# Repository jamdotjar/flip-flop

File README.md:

# T flip-flop
A transistor based T flip flop circuit. It uses 15 transistors, making 6 NAND gates. The design is based on an edge-triggered D flip-flop with one output fed into Data, and the user input acting as clock.

The design is a direct transfer of the logic-gate design into transistors. Each gate is fully built, which makes this a bit innefficent on part usage, but it's very simple design-wise. ( there's also lights for output, and a button for input ). The main challenge was figuring how to best use the limited resistor selection I had access to, without breaking the circit with a ton of random variance. 

For the PCB, I just tried to fit the schematic inside the logic diagram, to some degree of sucess. The design on the back is the result of asking as many people as possible what they thought should go there. I have ( almost ) no complaints.

I've yet to assemble, but I will update this page once I do.

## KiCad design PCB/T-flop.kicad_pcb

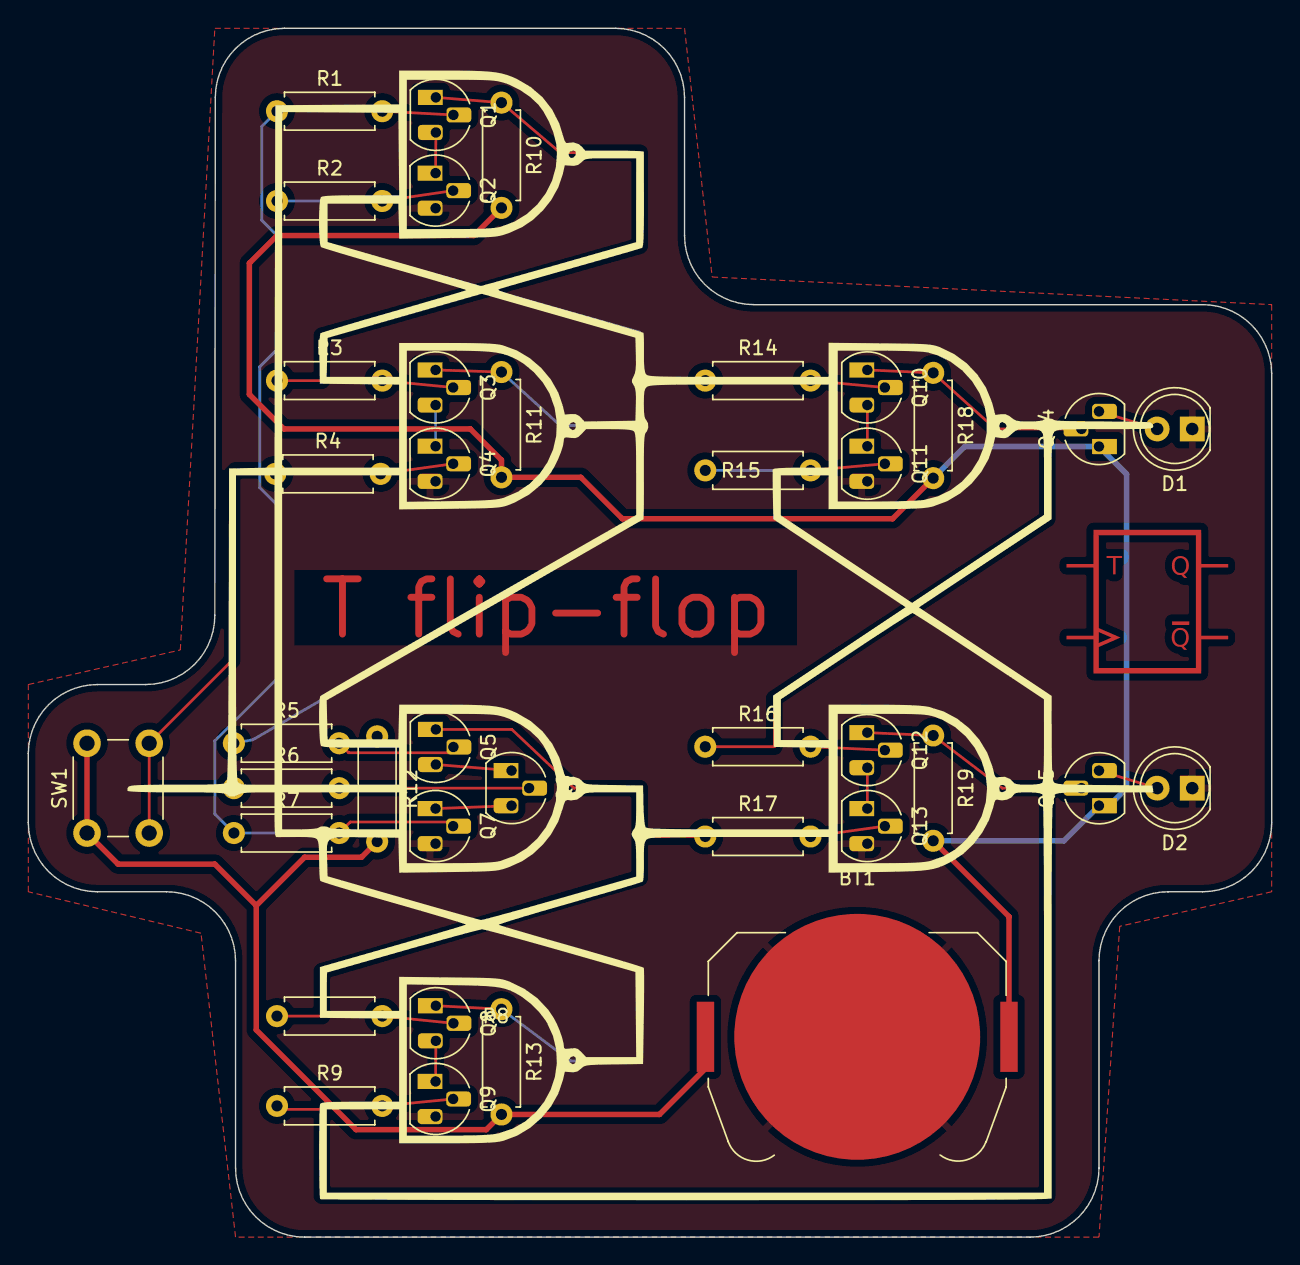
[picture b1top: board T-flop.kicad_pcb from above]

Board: 2 copper layers, 90.0 x 87.5 mm, 39 parts (1 on the bottom side), 31 nets.

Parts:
BT1: Battery_Cell; BatteryHolder_Keystone_3034_1x20mm
D1, D2: LED; LED_D5.0mm
Q1, Q2, Q3, Q4, Q5, Q6, Q7, Q8, Q9, Q10, Q11, Q12, Q13, Q14, Q15: NPN; TO-92L_HandSolder
R1, R2, R14, R15, R16, R17: 4.7k; R_Axial_DIN0207_L6.3mm_D2.5mm_P7.62mm_Horizontal
R3, R4, R5, R6, R7, R8, R10, R11, R12, R13, R18, R19: 220; R_Axial_DIN0207_L6.3mm_D2.5mm_P7.62mm_Horizontal
R9: 47k; R_Axial_DIN0207_L6.3mm_D2.5mm_P7.62mm_Horizontal
SW1: SW_Push; SW_PUSH_6mm
g: LOGO

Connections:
+3.3V: BT1.1 (+), Q14.1 (C), Q15.1 (C), R10.2, R11.2, R12.2, R13.2, R18.2, R19.2, SW1.1
GND: BT1.2 (-), D1.1 (K), D2.1 (K), Q2.3 (E), Q4.3 (E), Q7.3 (E), Q9.3 (E), Q11.3 (E), Q13.3 (E)
unnamed: D1.2 (A), Q14.3 (E)
unnamed: D2.2 (A), Q15.3 (E)
unnamed: Q1.2 (B), R1.2
unnamed: Q1.1 (C), R3.1, R10.1
unnamed: Q1.3 (E), Q2.1 (C)
unnamed: Q2.2 (B), R2.2
unnamed: Q3.2 (B), R3.2
unnamed: Q3.1 (C), R2.1, R5.1, R11.1, R14.1
unnamed: Q3.3 (E), Q4.1 (C)
unnamed: Q4.2 (B), R4.2
unnamed: Q5.2 (B), R5.2
unnamed: Q5.1 (C), R8.1, R12.1, R17.1
unnamed: Q5.3 (E), Q6.1 (C)
unnamed: Q6.2 (B), R6.2
unnamed: Q6.3 (E), Q7.1 (C)
unnamed: Q7.2 (B), R7.2
unnamed: Q8.2 (B), R8.2
unnamed: Q8.1 (C), R1.1, R7.1, R13.1
unnamed: Q8.3 (E), Q9.1 (C)
unnamed: Q9.2 (B), R9.2
unnamed: Q10.2 (B), R14.2
unnamed: Q10.1 (C), Q14.2 (B), R16.1, R18.1
unnamed: Q10.3 (E), Q11.1 (C)
unnamed: Q11.2 (B), R15.2
unnamed: Q12.2 (B), R16.2
unnamed: Q12.1 (C), Q15.2 (B), R9.1, R15.1, R19.1
unnamed: Q12.3 (E), Q13.1 (C)
unnamed: Q13.2 (B), R17.2
unnamed: R4.1, R6.1, SW1.2

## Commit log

2025-05-28 added pcb
